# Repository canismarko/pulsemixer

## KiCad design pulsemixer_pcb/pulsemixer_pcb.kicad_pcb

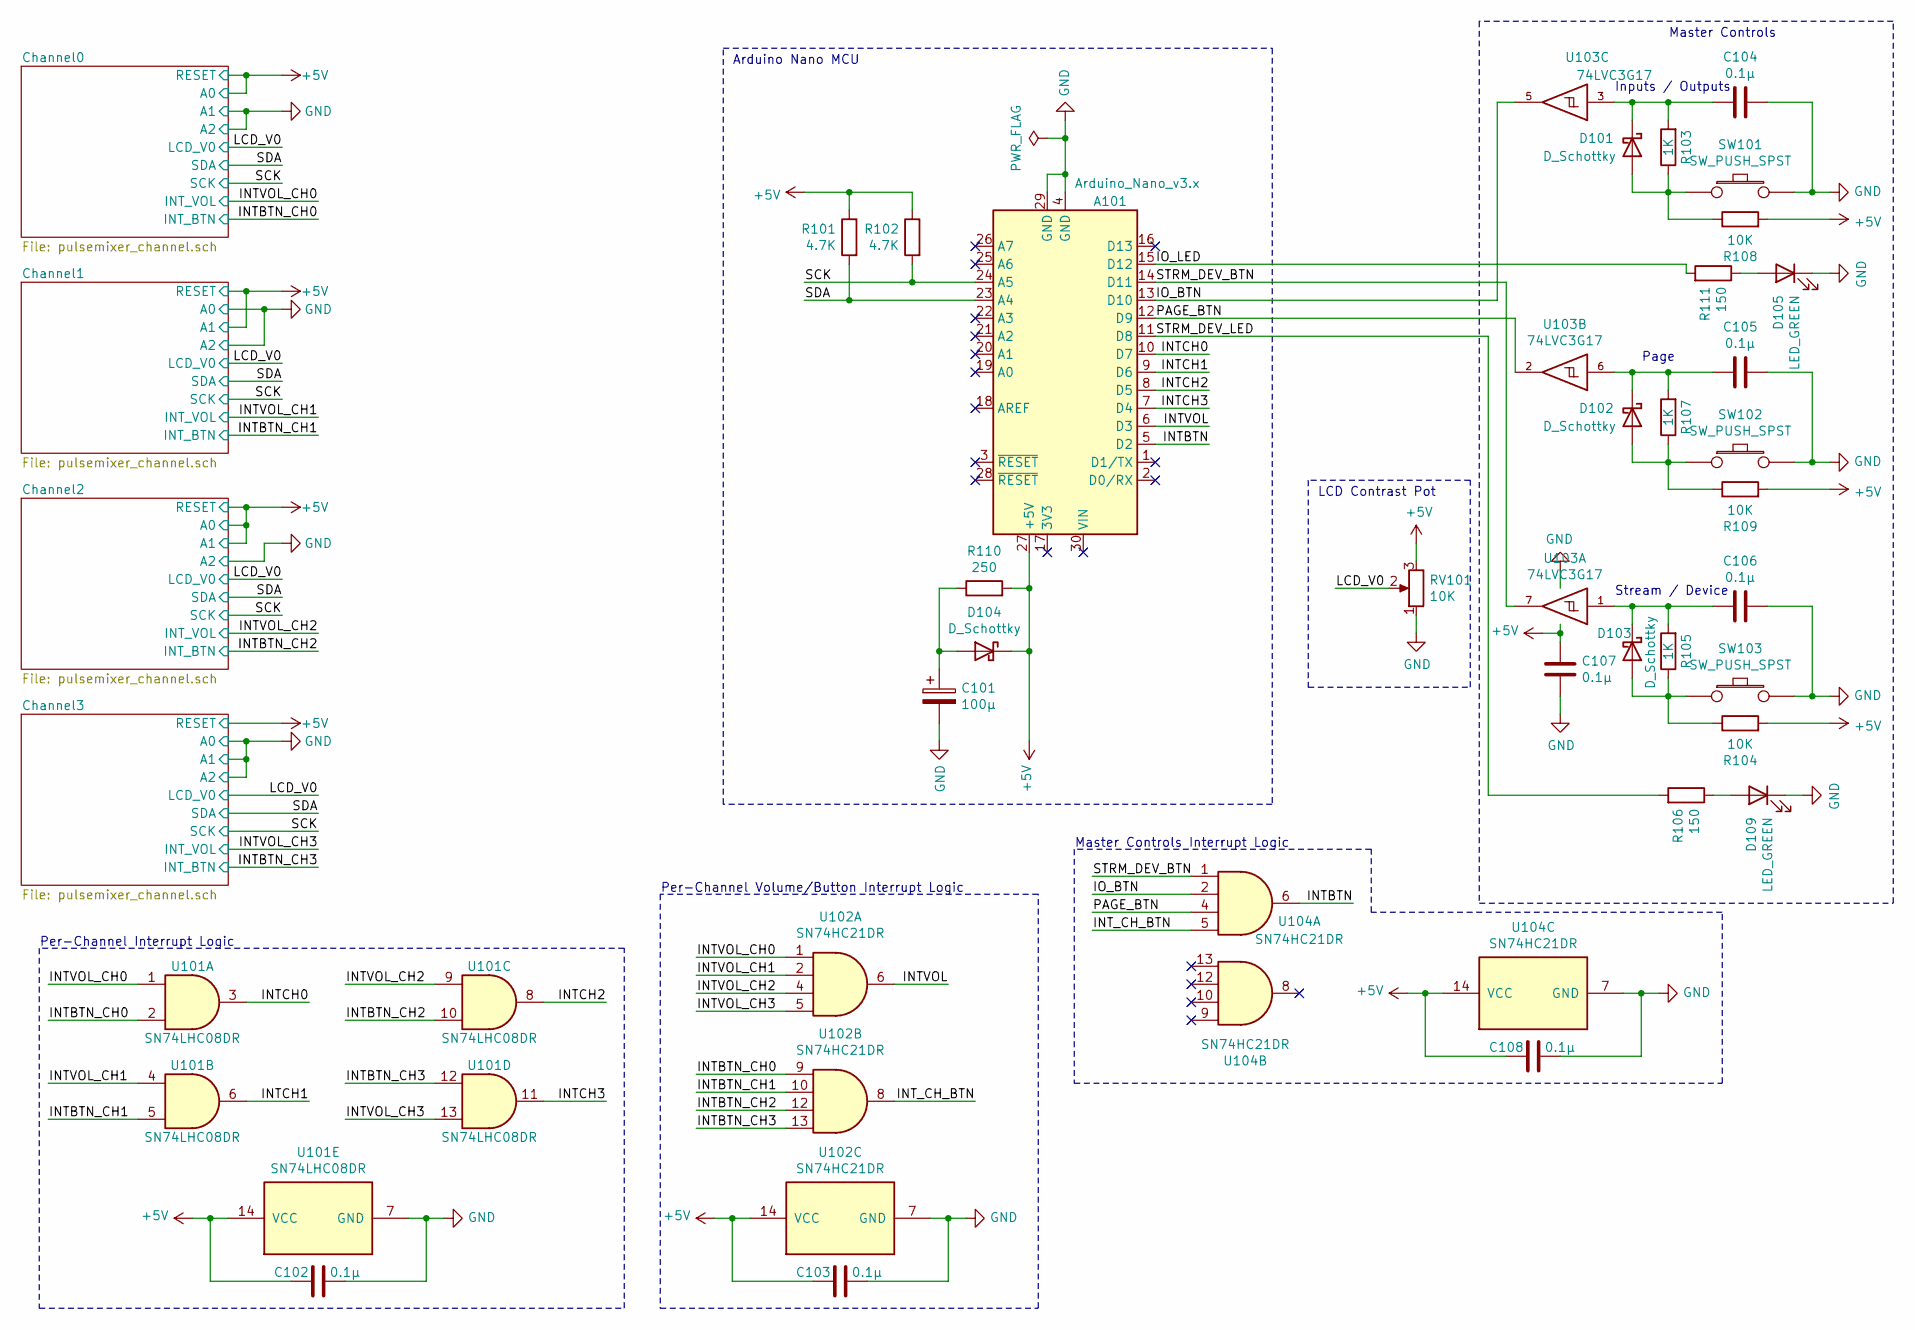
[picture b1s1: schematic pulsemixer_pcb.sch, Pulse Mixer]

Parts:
A101: Arduino_Nano_v3.x; SHIELD_ARDUINO_NANO
C101: 100µ; CP_Radial_D8.0mm_P3.50mm
C102, C103, C104, C105, C106, C107, C108: 0.1µ; C_0805_HandSoldering
D101, D102, D103, D104: D_Schottky; D_1206
D105, D109: LED_GREEN; LED_1206_HandSoldering
R101, R102: 4.7K; R_1206
R103, R105, R107: 1K; R_1206
R104, R108, R109: 10K; R_1206
R106, R111: 150; R_1206
R110: 250; R_1206
RV101: 10K; TRIM_3352T-1-103LF
SW101, SW102, SW103: SW_PUSH_SPST; SW_PUSH_6mm
U101: SN74LHC08DR; SOIC-14_3.9x8.7mm_Pitch1.27mm
U102, U104: SN74HC21DR; SOIC-14_3.9x8.7mm_Pitch1.27mm
U103: 74LVC3G17; SSOP-8_2.95x2.8mm_Pitch0.65mm

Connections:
+5V: A101.27 (+5V), C102.1, C103.1, C107.2, C108.2, D104.1 (K), R101.1, R102.1, R104.2, R108.2, R109.2, R110.2, RV101.3, U101.14 (VCC), U102.14 (VCC), U103.8 (VCC), U104.14 (VCC); also elsewhere on the board
/INTBTN: A101.5 (D2), U104.6
/INTBTN_CH0: U101.2, U102.9; also elsewhere on the board
/INTBTN_CH1: U101.5, U102.10; also elsewhere on the board
/INTBTN_CH2: U101.10, U102.12; also elsewhere on the board
/INTBTN_CH3: U101.12, U102.13; also elsewhere on the board
/INTCH0: A101.10 (D7), U101.3
/INTCH1: A101.9 (D6), U101.6
/INTCH2: A101.8 (D5), U101.8
/INTCH3: A101.7 (D4), U101.11
/INTVOL: A101.6 (D3), U102.6
/INTVOL_CH0: U101.1, U102.1; also elsewhere on the board
/INTVOL_CH1: U101.4, U102.2; also elsewhere on the board
/INTVOL_CH2: U101.9, U102.4; also elsewhere on the board
/INTVOL_CH3: U101.13, U102.5; also elsewhere on the board
/INT_CH_BTN: U102.8, U104.5
/IO_BTN: A101.13 (D10), U103.5, U104.2
/IO_LED: A101.15 (D12), R111.2
/LCD_V0: RV101.2; also elsewhere on the board
/PAGE_BTN: A101.12 (D9), U103.2, U104.4
/SCK: A101.24 (A5), R102.2; also elsewhere on the board
/SDA: A101.23 (A4), R101.2; also elsewhere on the board
/STRM_DEV_BTN: A101.14 (D11), U103.7, U104.1
/STRM_DEV_LED: A101.11 (D8), R106.2
GND: A101.4 (GND), A101.29 (GND), C101.2, C102.2, C103.2, C104.2, C105.2, C106.2, C107.1, C108.1, D105.1 (K), D109.1 (K), RV101.1, SW101.2, SW102.2, SW103.2, U101.7 (GND), U102.7 (GND), U103.4 (GND), U104.7 (GND); also elsewhere on the board
unnamed: C101.1, D104.2 (A), R110.1
unnamed: C104.1, D101.1 (K), R103.2, U103.3
unnamed: C105.1, D102.1 (K), R107.2, U103.6
unnamed: C106.1, D103.1 (K), R105.2, U103.1
unnamed: D101.2 (A), R103.1, R108.1, SW101.1
unnamed: D102.2 (A), R107.1, R109.1, SW102.1
unnamed: D103.2 (A), R104.1, R105.1, SW103.1
unnamed: D105.2 (A), R111.1
unnamed: D109.2 (A), R106.1

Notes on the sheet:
LCD Contrast Pot
Arduino Nano MCU
Per-Channel Interrupt Logic
Per-Channel Volume/Button Interrupt Logic
Master Controls
Stream / Device
Page
Inputs / Outputs
Master Controls Interrupt Logic

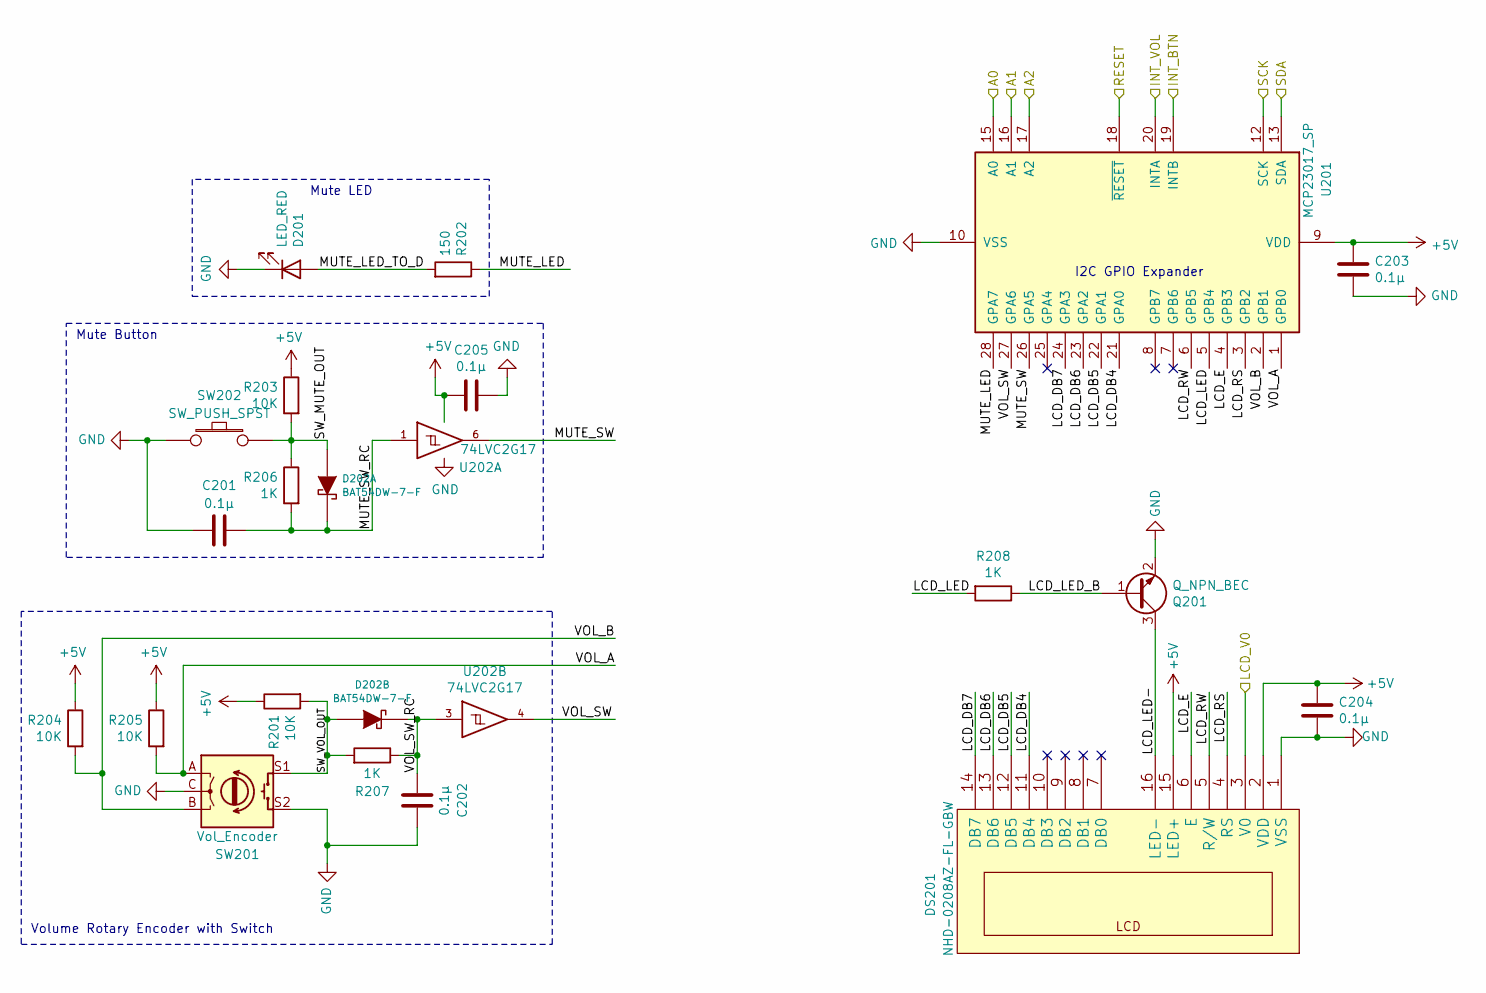
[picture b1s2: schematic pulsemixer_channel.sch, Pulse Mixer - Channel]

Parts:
C501, C502, C503, C504, C505: 0.1µ; C_0805_HandSoldering
D501: LED_RED; LED_1206_HandSoldering
D502: BAT54DW-7-F; Diode_Dual_SOT-23-6
DS501: NHD-0208AZ-FL-GBW
Q201: Q_NPN_BEC; SOT-23
R501, R503, R504, R505: 10K; R_1206
R502: 150; R_1206
R506, R507, R508: 1K; R_1206
SW501: Vol_Encoder; EN12-HS22AF18
SW502: SW_PUSH_SPST; SW_PUSH_6mm
U501: MCP23017_SP; DIP-28_W7.62mm
U502: 74LVC2G17; SOT-23-6

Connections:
+5V: C503.1, C504.1, C505.2, DS501.2 (VDD), DS501.15 (LED+), R501.1, R503.1, R504.1, R505.1, U501.9 (VDD), U501.15 (A0), U501.16 (A1), U501.18 (~RESET~), U502.5 (VCC); also elsewhere on the board
/Channel3/LCD_DB4: DS501.11 (DB4), U501.21 (GPA0)
/Channel3/LCD_DB5: DS501.12 (DB5), U501.22 (GPA1)
/Channel3/LCD_DB6: DS501.13 (DB6), U501.23 (GPA2)
/Channel3/LCD_DB7: DS501.14 (DB7), U501.24 (GPA3)
/Channel3/LCD_E: DS501.6 (E), U501.4 (GPB3)
/Channel3/LCD_LED: R508.2, U501.5 (GPB4)
/Channel3/LCD_RS: DS501.4 (RS), U501.3 (GPB2)
/Channel3/LCD_RW: DS501.5 (R/W), U501.6 (GPB5)
/Channel3/MUTE_LED: R502.1, U501.28 (GPA7)
/Channel3/MUTE_LED_TO_D: D501.2 (A), R502.2
/Channel3/MUTE_SW: U501.26 (GPA5), U502.6
/Channel3/MUTE_SW_RC: C501.2, D502.6 (C1), R506.2, U502.1
/Channel3/SW_MUTE_OUT: D502.1 (A1), R503.2, R506.1, SW502.1
/Channel3/SW_VOL_OUT: D502.4 (A2), R501.2, R507.2, SW501.S1
/Channel3/VOL_A: R505.2, SW501.A, U501.1 (GPB0)
/Channel3/VOL_B: R504.2, SW501.B, U501.2 (GPB1)
/Channel3/VOL_SW: U501.27 (GPA6), U502.4
/Channel3/VOL_SW_RC: C502.2, D502.3 (C2), R507.1, U502.3
/INTBTN_CH3: U501.19 (INTB); also elsewhere on the board
/INTVOL_CH3: U501.20 (INTA); also elsewhere on the board
/LCD_V0: DS501.3 (V0); also elsewhere on the board
/SCK: U501.12 (SCK); also elsewhere on the board
/SDA: U501.13 (SDA); also elsewhere on the board
GND: C501.1, C502.1, C503.2, C504.2, C505.1, D501.1 (K), DS501.1 (VSS), Q201.2 (E), SW501.C, SW501.S2, SW502.2, U501.10 (VSS), U501.17 (A2), U502.2 (GND); also elsewhere on the board

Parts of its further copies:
C201, C202, C203, C204, C205, C301, C302, C303, C304, C305, C401, C402, C403, C404, C405: 0.1µ; C_0805_HandSoldering
D201, D301, D401: LED_RED; LED_1206_HandSoldering
D202, D302, D402: BAT54DW-7-F; Diode_Dual_SOT-23-6
DS201, DS301, DS401: NHD-0208AZ-FL-GBW
Q301, Q401, Q501: Q_NPN_BEC; SOT-23
R201, R203, R204, R205, R301, R303, R304, R305, R401, R403, R404, R405: 10K; R_1206
R202, R302, R402: 150; R_1206
R206, R207, R208, R306, R307, R308, R406, R407, R408: 1K; R_1206
SW201, SW301, SW401: Vol_Encoder; EN12-HS22AF18
SW202, SW302, SW402: SW_PUSH_SPST; SW_PUSH_6mm
U201, U301, U401: MCP23017_SP; DIP-28_W7.62mm
U202, U302, U402: 74LVC2G17; SOT-23-6

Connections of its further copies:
+5V: C203.1, C204.1, C205.2, C303.1, C304.1, C305.2, C403.1, C404.1, C405.2, DS201.2 (VDD), DS201.15 (LED+), DS301.2 (VDD), DS301.15 (LED+), DS401.2 (VDD), DS401.15 (LED+), R201.1, R203.1, R204.1, R205.1, R301.1, R303.1, R304.1, R305.1, R401.1, R403.1, R404.1, R405.1, U201.9 (VDD), U201.18 (~RESET~), U202.5 (VCC), U301.9 (VDD), U301.15 (A0), U301.18 (~RESET~), U302.5 (VCC), U401.9 (VDD), U401.16 (A1), U401.18 (~RESET~), U402.5 (VCC); also elsewhere on the board
/Channel0/LCD_DB4: DS201.11 (DB4), U201.21 (GPA0)
/Channel0/LCD_DB5: DS201.12 (DB5), U201.22 (GPA1)
/Channel0/LCD_DB6: DS201.13 (DB6), U201.23 (GPA2)
/Channel0/LCD_DB7: DS201.14 (DB7), U201.24 (GPA3)
/Channel0/LCD_E: DS201.6 (E), U201.4 (GPB3)
/Channel0/LCD_LED: R208.2, U201.5 (GPB4)
/Channel0/LCD_RS: DS201.4 (RS), U201.3 (GPB2)
/Channel0/LCD_RW: DS201.5 (R/W), U201.6 (GPB5)
/Channel0/MUTE_LED: R202.1, U201.28 (GPA7)
/Channel0/MUTE_LED_TO_D: D201.2 (A), R202.2
/Channel0/MUTE_SW: U201.26 (GPA5), U202.6
/Channel0/MUTE_SW_RC: C201.2, D202.6 (C1), R206.2, U202.1
/Channel0/SW_MUTE_OUT: D202.1 (A1), R203.2, R206.1, SW202.1
/Channel0/SW_VOL_OUT: D202.4 (A2), R201.2, R207.2, SW201.S1
/Channel0/VOL_A: R205.2, SW201.A, U201.1 (GPB0)
/Channel0/VOL_B: R204.2, SW201.B, U201.2 (GPB1)
/Channel0/VOL_SW: U201.27 (GPA6), U202.4
/Channel0/VOL_SW_RC: C202.2, D202.3 (C2), R207.1, U202.3
/Channel1/LCD_DB4: DS301.11 (DB4), U301.21 (GPA0)
/Channel1/LCD_DB5: DS301.12 (DB5), U301.22 (GPA1)
/Channel1/LCD_DB6: DS301.13 (DB6), U301.23 (GPA2)
/Channel1/LCD_DB7: DS301.14 (DB7), U301.24 (GPA3)
/Channel1/LCD_E: DS301.6 (E), U301.4 (GPB3)
/Channel1/LCD_LED: R308.2, U301.5 (GPB4)
/Channel1/LCD_LED-: DS301.16 (LED-), Q301.3 (C)
/Channel1/LCD_LED_B: Q301.1 (B), R308.1
/Channel1/LCD_RS: DS301.4 (RS), U301.3 (GPB2)
/Channel1/LCD_RW: DS301.5 (R/W), U301.6 (GPB5)
/Channel1/MUTE_LED: R302.1, U301.28 (GPA7)
/Channel1/MUTE_LED_TO_D: D301.2 (A), R302.2
/Channel1/MUTE_SW: U301.26 (GPA5), U302.6
/Channel1/MUTE_SW_RC: C301.2, D302.6 (C1), R306.2, U302.1
/Channel1/SW_MUTE_OUT: D302.1 (A1), R303.2, R306.1, SW302.1
/Channel1/SW_VOL_OUT: D302.4 (A2), R301.2, R307.2, SW301.S1
/Channel1/VOL_A: R305.2, SW301.A, U301.1 (GPB0)
/Channel1/VOL_B: R304.2, SW301.B, U301.2 (GPB1)
/Channel1/VOL_SW: U301.27 (GPA6), U302.4
/Channel1/VOL_SW_RC: C302.2, D302.3 (C2), R307.1, U302.3
/Channel2/LCD_DB4: DS401.11 (DB4), U401.21 (GPA0)
/Channel2/LCD_DB5: DS401.12 (DB5), U401.22 (GPA1)
/Channel2/LCD_DB6: DS401.13 (DB6), U401.23 (GPA2)
/Channel2/LCD_DB7: DS401.14 (DB7), U401.24 (GPA3)
/Channel2/LCD_E: DS401.6 (E), U401.4 (GPB3)
/Channel2/LCD_LED: R408.2, U401.5 (GPB4)
/Channel2/LCD_LED-: DS401.16 (LED-), Q401.3 (C)
/Channel2/LCD_LED_B: Q401.1 (B), R408.1
/Channel2/LCD_RS: DS401.4 (RS), U401.3 (GPB2)
/Channel2/LCD_RW: DS401.5 (R/W), U401.6 (GPB5)
/Channel2/MUTE_LED: R402.1, U401.28 (GPA7)
/Channel2/MUTE_LED_TO_D: D401.2 (A), R402.2
/Channel2/MUTE_SW: U401.26 (GPA5), U402.6
/Channel2/MUTE_SW_RC: C401.2, D402.6 (C1), R406.2, U402.1
/Channel2/SW_MUTE_OUT: D402.1 (A1), R403.2, R406.1, SW402.1
/Channel2/SW_VOL_OUT: D402.4 (A2), R401.2, R407.2, SW401.S1
/Channel2/VOL_A: R405.2, SW401.A, U401.1 (GPB0)
/Channel2/VOL_B: R404.2, SW401.B, U401.2 (GPB1)
/Channel2/VOL_SW: U401.27 (GPA6), U402.4
/Channel2/VOL_SW_RC: C402.2, D402.3 (C2), R407.1, U402.3
/INTBTN_CH0: U201.19 (INTB); also elsewhere on the board
/INTBTN_CH1: U301.19 (INTB); also elsewhere on the board
/INTBTN_CH2: U401.19 (INTB); also elsewhere on the board
/INTVOL_CH0: U201.20 (INTA); also elsewhere on the board
/INTVOL_CH1: U301.20 (INTA); also elsewhere on the board
/INTVOL_CH2: U401.20 (INTA); also elsewhere on the board
/LCD_V0: DS201.3 (V0), DS301.3 (V0), DS401.3 (V0); also elsewhere on the board
/SCK: U201.12 (SCK), U301.12 (SCK), U401.12 (SCK); also elsewhere on the board
/SDA: U201.13 (SDA), U301.13 (SDA), U401.13 (SDA); also elsewhere on the board
GND: C201.1, C202.1, C203.2, C204.2, C205.1, C301.1, C302.1, C303.2, C304.2, C305.1, C401.1, C402.1, C403.2, C404.2, C405.1, D201.1 (K), D301.1 (K), D401.1 (K), DS201.1 (VSS), DS301.1 (VSS), DS401.1 (VSS), Q301.2 (E), Q401.2 (E), Q501.2 (E), SW201.C, SW201.S2, SW202.2, SW301.C, SW301.S2, SW302.2, SW401.C, SW401.S2, SW402.2, U201.10 (VSS), U201.15 (A0), U201.16 (A1), U201.17 (A2), U202.2 (GND), U301.10 (VSS), U301.16 (A1), U301.17 (A2), U302.2 (GND), U401.10 (VSS), U401.15 (A0), U401.17 (A2), U402.2 (GND); also elsewhere on the board

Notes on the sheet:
Volume Rotary Encoder with Switch
Mute Button
Mute LED
I2C GPIO Expander

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
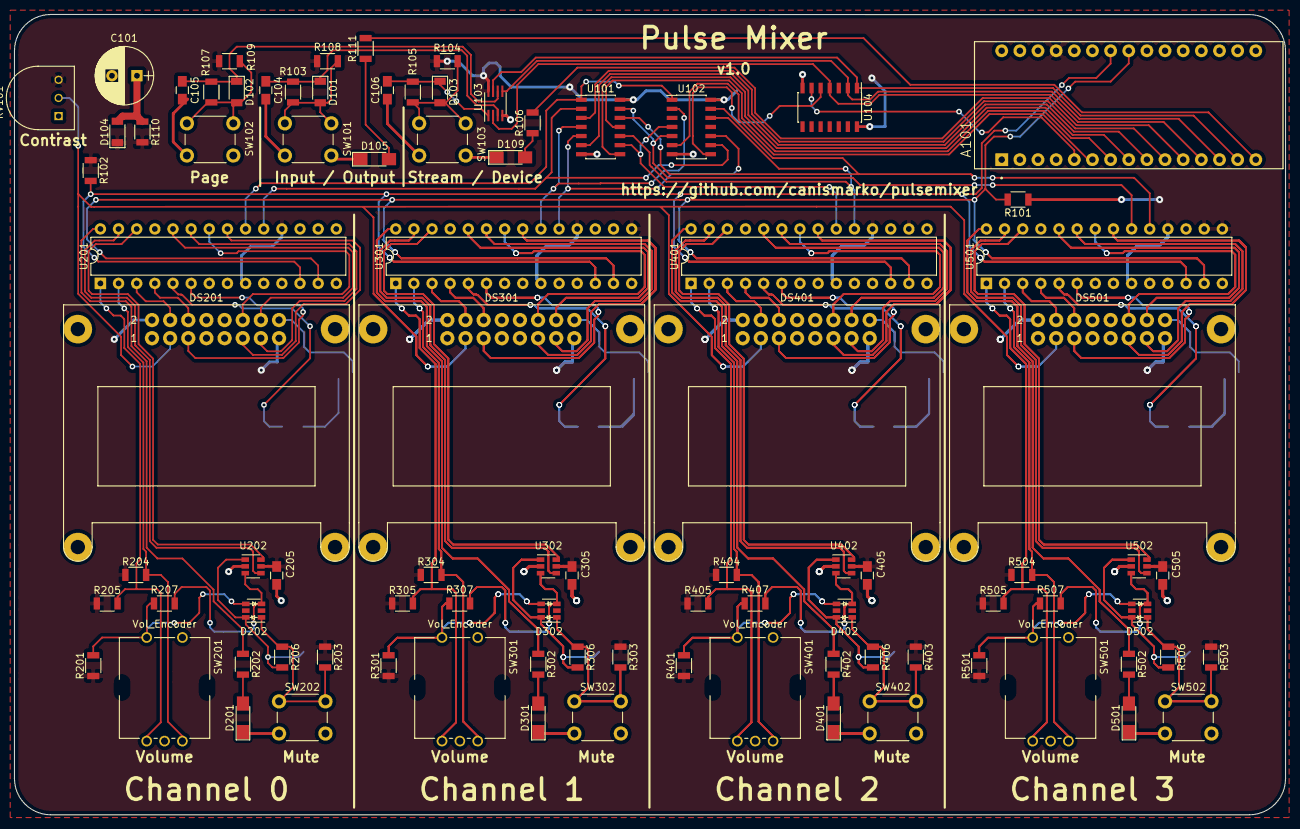
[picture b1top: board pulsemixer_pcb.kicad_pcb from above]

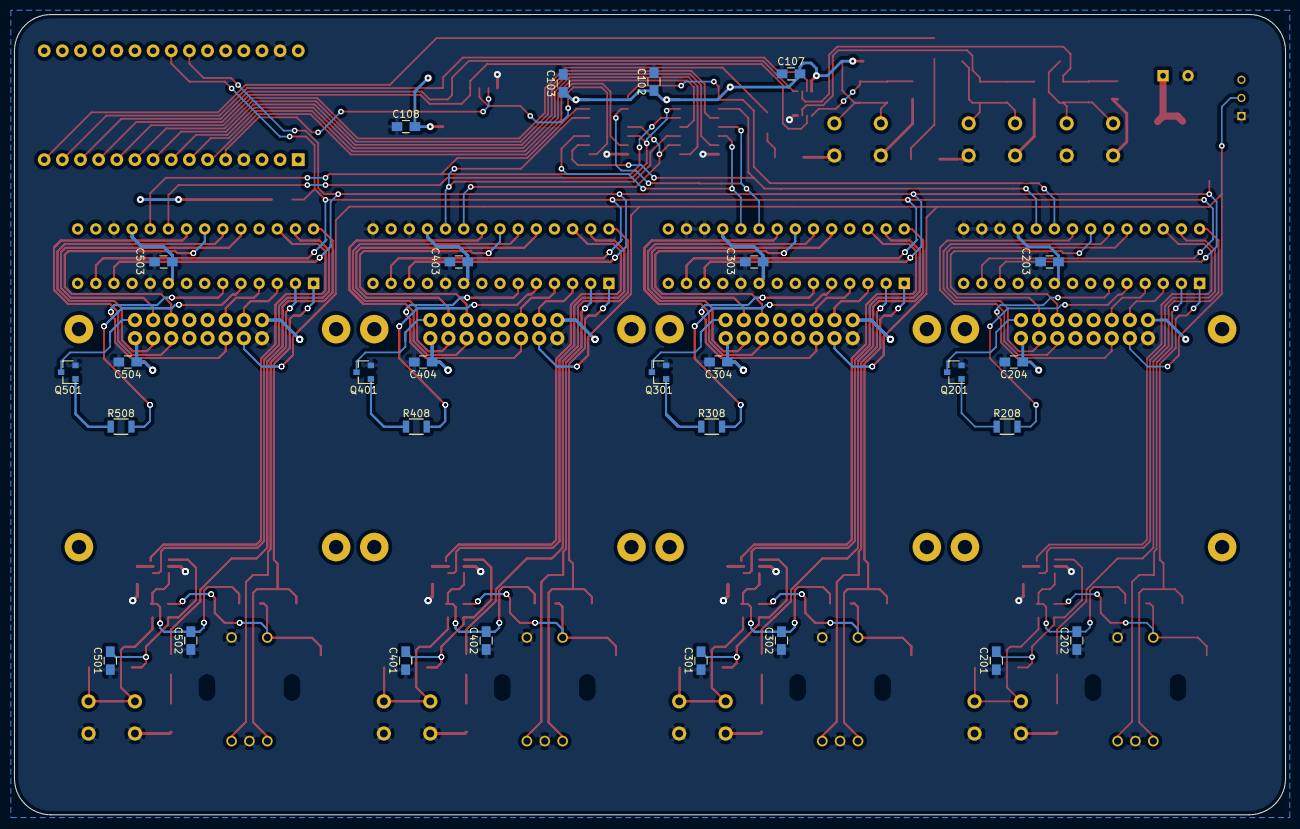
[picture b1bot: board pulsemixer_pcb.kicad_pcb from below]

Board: 2 copper layers, 177.9 x 112.0 mm, 118 parts (28 on the bottom side), 114 nets.

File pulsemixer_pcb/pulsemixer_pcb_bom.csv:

Id,Digi-Key Ln,Designator,Package,Quantity,Designation,Supplier and ref,
1,7,"DS201,DS401,DS501,DS301",NHD-0208AZ-FL-GBW,4,NHD-0208AZ-FL-GBW,‎NHD-0208AZ-FL-GBW,
2,3,"SW201,SW301,SW401,SW501",EN12-HS22AF18,4,Vol_Encoder,‎EN12-HS22AF18,
3,10,"C201,C202,C204,C203,C505,C405,C305,C205,C103,C102,C401,C402,C403,C404,C501,C502,C503,C504,C301,C302,C303,C304,C104,C105,C106,C107",C_0805_HandSoldering,27,0.1µ,‎C0805C104Z3VACTU,50 for price break
4,2,"U201,U401,U501,U301",DIP-28_W7.62mm,4,MCP23017_SP,‎MCP23017-E/SP,
5,20,"D201,D401,D501,D301",LED_1206_HandSoldering,4,LED_RED,CMD15-21VRD/TR8 ,Vf=2.1V @ 20mA
6,11,"SW202,SW103,SW402,SW502,SW302,SW101,SW102",SW_PUSH_6mm,7,SW_PUSH_SPST,PTS645SH43-2 LFS,
7,12,"U102, U104",SOIC-14_3.9x8.7mm_Pitch1.27mm,2,SN74HC21DR,SN74HC21DR,
8,4,U101,SOIC-14_3.9x8.7mm_Pitch1.27mm,1,SN74LHC08DR,SN74HC08DR,
9,22,A101,SHIELD_ARDUINO_NANO,1,Arduino_Nano_v3.x,‎A000005‎,Not ordered since I already have one
10,21,"D109,D105",LED_1206_HandSoldering,2,LED_GREEN,CMD15-21VGD/TR8,Vf=2.1V @ 20mA
11,6,RV101,TRIM_3352T-1-103LF,1,10K,‎3352T-1-103LF‎,
12,13,"D101,D102,D103,D104",D_1206,4,D_Schottky,SD1206S040S0R5 ,
13,8,U103,SSOP-8_2.95x2.8mm_Pitch0.65mm,1,74LVC3G17,‎SN74LVC3G17DCTR,
14,5,"D202,D302,D402,D502",Diode_Dual_SOT-23-6,4,BAT54DW-7-F,BAT54DW-7-F,
15,14,"Q201,Q301,Q401,Q501",SOT-23,4,Q_NPN_BEC,MMBT3904-7-F,
16,9,"U202,U302,U402,U502",SOT-23-6,4,74LVC2G17,‎SN74LVC2G17DBVR,
17,1,C101,CP_Radial_D8.0mm_P3.50mm,1,100µ,‎UMV1E100MFD1TP,
18,15,"R101,R102",R_1206,2,4.7K,RC1206FR-074K7L,
19,16,"R103,R105,R107,R206,R207,R208,R306,R307,R308,R406,R407,R408,R506,R507,R508",R_1206,15,1K,RNCP1206FTD1K00,
20,17,"R104,R108,R109,R201,R203,R204,R205,R301,R303,R304,R305,R401,R403,R404,R405,R501,R503,R504,R505",R_1206,19,10K,RC1206FR-0710KL,
21,18,"R106,R202,R302,R402,R502,R111",R_1206,6,150,311-150FRCT-ND ,
22,19,R110,R_1206,1,250,RMCF1206FT270R ,
23,,,6mm diameter with 4.5mm flat,4,Knob,1722-1238-ND ,

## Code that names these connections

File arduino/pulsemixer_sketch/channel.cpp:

#include "Arduino.h"
#include "channel.h"
#include "GPIO.h"

// #define DEBUG

#define MUTE_LED 0x8000 // B10000000 00000000
#define VOL_SW   0x4000 // B01000000 00000000
#define MUTE_SW  0x2000 // B00100000 00000000
#define VOL_A    0x0001 // B00000000 00000001
#define VOL_B    0x0002 // B00000000 00000010
#define VOLS     (VOL_A | VOL_B)

#define MIN_VOL 0
#define MAX_VOL 100

volatile boolean isr_is_running = false;


const byte RotaryDecodeTable[4][4] = {  // Declare array RotaryDecodeTable
{B00, B10, B01, B11},
{B01, B00, B11, B10},
{B10, B11, B00, B01},
{B11, B01, B10, B00}
};


gpio_bank Channel::getAddr() {
  return _addr;
}


void Channel::setupI2C(gpio_bank new_addr) {
  // Save the I2C address for later operations
  _addr = new_addr;
  _gpio.setupI2C(_addr);
  // _short_name = "Addr: " + String(_addr, HEX);
  // Set pins to read/write
  // Input pins
  gpio_full iodir = 0x0000;
  gpio_full io_mask = MUTE_LED | VOL_SW | MUTE_SW | VOL_A | VOL_B;
  iodir = iodir | MUTE_SW;
  iodir = iodir | VOL_SW;
  iodir = iodir | VOL_A;
  iodir = iodir | VOL_B;
  // Output pins
  iodir = iodir & ~MUTE_LED;
  _gpio.setRegister(IODIRA, iodir, io_mask);

  // Set up hardware interrupts
  // writeMCP(_addr, GPINTENA, (gpio_bank) B00000000);
  // writeMCP(_addr, GPINTENB, (gpio_bank) B00000000);
  // writeMCP(_addr, INTCONA, (gpio_bank) 0x00);
  // writeMCP(_addr, INTCONB, (gpio_bank) B00000000);
  _gpio.enableInterrupts(VOL_A | VOL_B);
  _gpio.enableInterrupts(VOL_SW | MUTE_SW);

  // Make buttons report 1 when pressed
  // writeMCP(_addr, IPOLB, (gpio_bank) B00000011);

  // Prepare the LCD to display channel name, etc.
  _lcd.setupI2C(_addr);
  showChannelName();

}

void Channel::showChannelName() {
  _lcd.setLineOne(_short_name);
}
  

void Channel::writeGPIO(gpio_full data) {
  _gpio.writeMCP(_addr, GPIOA, data);
}


void Channel::setInterruptFlag() {
  // Checker to see if we're already in an ISR
  if(isr_is_running || _gpio.is_busy()) return; //we have been interrupted while already processing an interrupt - ignore this ocurrence
  _interrupt_flag = true;
  isr_is_running = true;
  interrupts(); //re-enable interrupts so that interrupt-based functions can be used inside this function
  // Check if this is a volume knob event
  gpio_full int_state = readInterruptState();
  // Determine which inputs triggered the interrupt
  // gpio_full int_triggered = readInterruptFlags();
  // Disable interrupts so we can keep running this function
  
  isr_is_running = false;
  // Extract the volume rotary encoder A/B bits
  byte new_vols = (int_state & VOLS);
  byte vol_move = RotaryDecodeTable[_vol_old_pins][new_vols]; // used RotaryDecodeTable to decide movement, if any
  _vol_old_pins = new_vols;
  // Set the pending volume to the current volume if it's not dirty
  if (!_volume_dirty)
    pending_volume = _volume;
  if (vol_move == B10){ // if result was move right (CW), increment counter
    pending_volume += 3;
    _volume_dirty = true;
  }
  if (vol_move == B01){ // if result was move left (anti-CW), decrement counter
    pending_volume -= 3;
    _volume_dirty = true;
  }
  noInterrupts(); //turn off interrupts so we can't be interrupted while resetting our special variable
  
}


void Channel::setVolume(int new_volume) {
  unsigned long current_time = micros();
  if (current_time - _last_volume_change > 10000) {
    if (new_volume < MIN_VOL) {
      new_volume = MIN_VOL;
    } else if (new_volume > MAX_VOL) {
      new_volume = MAX_VOL;
    }
    #ifdef DEBUG
    Serial.print("Setting new volume ");
    Serial.print(_id);
    Serial.print(": ");
    Serial.println(new_volume);
    #endif
    _volume = new_volume;
    pending_volume = _volume;
    // Update the LCD
    _lcd.showVolume(_volume);
    _lcd.turnOnLED();
    // Send new volume to the host
    Serial.print("!set volume ");
    Serial.print(_id);
    Serial.print(" ");
    Serial.println(_volume);
  }
  _last_volume_change = current_time;
}


void Channel::bumpVolume(int vol_change) {
  setVolume(_volume + vol_change);
}


void Channel::updateOutputs() {
  _lcd.updateDisplay();
}


bool Channel::processInterrupts() {
  if (_volume_dirty) {
    _volume_dirty = false;
    #ifdef DEBUG
    Serial.print("Volume changed: ");
    Serial.println(pending_volume);
    #endif
    // _volume = bumpVolume(pending_volume);
    Channel::setVolume(pending_volume);
  }
  // Returns true if the volume encoder was moved
  if (_interrupt_flag) {
    _interrupt_flag = false;
    gpio_full int_state = readInterruptState();
    // Determine which inputs triggered the interrupt
    gpio_full int_triggered = readInterruptFlags();
    // Extract the volume rotary encoder A/B bits
//    byte new_vols = (int_state & VOLS);
//    if (new_vols != _vol_old_pins)
//      _last_volume_touched = micros();
//    byte vol_move = RotaryDecodeTable[_vol_old_pins][new_vols]; // used RotaryDecodeTable to decide movement, if any
//    _vol_old_pins = new_vols;
//    if (vol_move == B10){ // if result was move right (CW), increment counter
//      bumpVolume(1);
//    }
//    if (vol_move == B01){ // if result was move left (anti-CW), decrement counter
//      bumpVolume(-1);
//    }
  
    if (~int_state & MUTE_SW) {
      // Serial.println("Mute switch pressed");
      toggleMute();
    }
    if (~int_state & VOL_SW) {
      // Serial.println("Volume switch pressed");
      _lcd.turnOnLED();
    }
  }
  return (micros() - _last_volume_touched < 20000);
}


gpio_full Channel::readInterruptState() {
  // Read the state of all the GPIO expander pins when the last
  // interrupt was triggered. This also clears the
  // interrupt pin.
  gpio_full int_state = _gpio.readFullRegister(INTCAPA);
  return int_state;
}

gpio_full Channel::readInterruptFlags() {
  // Read the interrupt flags showing which pins in the GPIO expander 
  // triggered the last interrupt. This does not clear the
  // interrupt pin.
  gpio_full int_state = _gpio.readFullRegister(INTFA);
  return int_state;
}



void Channel::setMute(bool new_mute_state) {
  _isMuted = new_mute_state;
  if (_isMuted) {
    _gpio.setPins(GPIOA, 0xFFFF, MUTE_LED);
    _lcd.setLineTwo("Muted   ");
  } else {
    _gpio.setPins(GPIOA, 0x0000, MUTE_LED);
    _lcd.setLineTwo("Unmuted ");
  }
  _lcd.writeLines();
  _lcd.turnOnLED();
}


void Channel::toggleMute() {
  bool new_mute_state = !_isMuted;
  setMute(new_mute_state);
  // Notify the host
  Serial.print("!mute ");
  Serial.print(_id);
  Serial.print(" ");
  Serial.println(_isMuted);
}


void Channel::setShortName(String new_name) {
  _short_name = new_name;
  showChannelName();
}

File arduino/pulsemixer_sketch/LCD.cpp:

#include "LCD.h"
#include "GPIO.h"

#define LCD_DB      0x0FF0 // B00001111 11110000 // 8-bit mode
#define LCD_DB_4BIT 0x0F00 // B00001111 00000000 // 4-bit mode
#define LCD_ENABLE  0x0008 // B00000000 00001000
#define LCD_RS      0x0004 // B00000000 00000100
#define LCD_RW      0x0020 // B00000000 00100000
#define LCD_LED     0x0010 // B00000000 00010000
#define LCD_DATA LCD_DB_4BIT | LCD_ENABLE | LCD_RS | LCD_RW
#define LCD_ALL LCD_DATA | LCD_LED

#define LED_TIMEOUT 5000 // In milliseconds
#define LCD_WIDTH 8

// #define DEBUG


void LCD::setupI2C(gpio_bank addr)
{
  _addr = addr;
  _gpio.setupI2C(addr);
  // Set GPIO I/O settings
  gpio_full iodir = 0x0000;
  iodir = iodir & ~LCD_DB_4BIT;
  iodir = iodir & ~LCD_ENABLE;
  iodir = iodir & ~LCD_LED;
  iodir = iodir & ~LCD_RW;
  gpio_full iodir_mask = LCD_ALL;
  _gpio.setRegister(IODIRA, iodir, iodir_mask);
  // Initalize the LCD display
  this -> _init();
  // Start with the LEDs off
  this -> turnOffLED();
}


void LCD::setLineOne(String new_text)
{
  // Add extra spaces as necessary
  while(new_text.length() < LCD_WIDTH) {
    new_text += ' ';
  }
  #ifdef DEBUG
  Serial.print("Setting line two to: ");
  Serial.println(new_text);
  #endif
  _line_one_text = new_text;
}


void LCD::setLineTwo(String new_text)
{
  // Add extra spaces as necessary
  while(new_text.length() < LCD_WIDTH) {
    new_text += ' ';
  }
  #ifdef DEBUG
  Serial.print("Setting line two to: ");
  Serial.println(new_text);
  #endif
  _line_two_text = new_text;
}


void LCD::showVolume(int new_vol)
{
  unsigned char line_length;
  String message = String(new_vol) + "%    ";
  // Pad the message with leading spaces
  for (int i=0; i<9-message.length(); i++) {
    message = " " + message;
  }
  setLineTwo(message);
  this->writeLines();
}


void LCD::updateDisplay()
// Check if the display has changed since it was last refreshed
// If nothing has changed, the display will not be written to.
{
  if (this->led_on) {
    // Check if the LED timer has expired
    unsigned long current_timer = millis() - led_on_time;
    if (current_timer > LED_TIMEOUT) {
      // Timeout has expired, so turn off the LED
      #ifdef DEBUG
      Serial.println("LED timer expired.");
      #endif
      setLineTwo("        ");
      this->writeLines();
      turnOffLED();
    }
  }
  this->writeLines();
}


void LCD::turnOnLED()
{
  
  this->led_on_time = millis();
  if (!this->led_on) {
    this->led_on = true;
    this->setLED(HIGH);
  }
  #ifdef DEBUG
  Serial.print("Turned on LED ");
  Serial.print(_addr, HEX);
  Serial.print(": ");
  Serial.println(this->led_on);
  #endif
  
}


void LCD::turnOffLED()
{
  this->led_on = false;
  this->setLED(LOW);
  #ifdef DEBUG
  Serial.print("Turned off LED ");
  Serial.print(this->_addr, HEX);
  Serial.print(": ");
  Serial.println(this->led_on);
  #endif
}


void LCD::setLED(bool setOn)
{
  gpio_full newState;
  if (setOn) {
    newState = 0xFFFF;
  }
  else {
    newState = 0x0000;
  }
  #ifdef DEBUG
  Serial.print("Sending LED command: ");
  Serial.println(newState, HEX);
  #endif
  this->_gpio.setPins(GPIOA, newState, LCD_LED);
  delay(500);
}


unsigned char LCD::_send_message(String message, String old_message, unsigned char cursor_offset)
{
  unsigned char line_length, cursor_pos=-1, characters_changed=0;
  line_length = min(message.length(), LCD_WIDTH);
  for (int i=0; i<line_length; i++) {
    // Check if the character needs to be updated
    if (message[i] != old_message[i]) {
      if ((i+cursor_offset) != cursor_pos) {
        // We've skipped some characters to update the cursor position
        cursor_pos = i+cursor_offset;
        _moveCursor(cursor_pos);
      }
      #ifdef DEBUG
      Serial.print("Printing char ");
      Serial.print(i);
      Serial.print(" (");
      Serial.print(cursor_pos);
      Serial.print(") to '");
      Serial.print(message[i]);
      Serial.println("'");
      #endif
      _send_data(message[i]);
      characters_changed += 1;
      cursor_pos++;
    }
  }
  return characters_changed;
}


void LCD::writeLines()
{
  
  if (_is_ready) {
    unsigned char blocks_changed=0;
    // Return home
    // _send_command(0x02); // B00000010
    _moveCursor(0);
    // Write line 1
    blocks_changed += _send_message(_line_one_text, _line_one_text_old, 0);
    // Write line 2
    blocks_changed += _send_message(_line_two_text, _line_two_text_old, 40);
    // Save the written text for next time
    _line_one_text_old = _line_one_text;
    _line_two_text_old = _line_two_text;
    // Light up the LED if anything changed
    if (blocks_changed > 0) {
      this->turnOnLED();
    }
  }
}


void LCD::_moveCursor(unsigned char pos)
{
  _send_command(128 + pos);
}


void LCD::_send_command(gpio_bank command, bool is4bit=true)
{
  gpio_full gpioPins = this->_gpio.readPins();
  // Put first (MSB) 4-bits of command on output port
  gpioPins = setBits(gpioPins, command << 4, LCD_DB_4BIT);
  // D/I=LOW : send instruction (D_I =0)
  gpioPins = setBits(gpioPins, 0x0000, LCD_RS);
  // R/W=LOW : Write (R_W =0)
  gpioPins = setBits(gpioPins, 0x0000, LCD_RW);
  // Clock enable: falling edge
  this->_gpio.setPins(GPIOA, gpioPins, LCD_ALL);
  _trigger();
  // Send the second (LSB) 4-bit chunk
  if (is4bit) {
    gpioPins = setBits(gpioPins, command << 8, LCD_DB_4BIT);
    this->_gpio.setPins(GPIOA, gpioPins, LCD_ALL);
    _trigger();
  }
}


void LCD::_send_data(gpio_bank data)
{
  gpio_full gpioPins = 0x0000;
  // Put first (MSB) 4-bits of data on output port
  gpioPins = setBits(gpioPins, data << 4, LCD_DB_4BIT);
  // D/I=HIGH : send data (D_I =1)
  gpioPins = setBits(gpioPins, 0xFFFF, LCD_RS);
  // R/W=LOW : Write (R_W =0)
  this -> _gpio.setPins(GPIOA, gpioPins, LCD_DATA);
  //Clock enable: falling edge
  _trigger();
  // Send the second (LSB) 4-bit chunk
  gpioPins = setBits(gpioPins, data << 8, LCD_DB_4BIT);
  this->_gpio.setPins(GPIOA, gpioPins, LCD_DATA);
  _trigger();
}


void LCD::_init()
{
  this -> _gpio.setPins(GPIOA, 0x0000, LCD_ENABLE);
  //Wait >40 msec after power is applied
  delay(100);
  // command 0x30 = Wake up
  _send_command(0x30, false); // B00110000
  // must wait 5ms, busy flag not available
  delay(30);
  // command 0x30 = Wake up #2
  _send_command(0x30, false); // B00110000
  // must wait 160us, busy flag not available
  delay(10);
  // command 0x30 = Wake up #3
  _send_command(0x30, false); // B00110000
  //must wait 160us, busy flag not available
  delay(10);
  // Function set: 4-bit
  _send_command(0x20, false); // B00100000
  // Function set: 4-bit/2-line
  _send_command(0x28); // B00101000
  // Set cursor
  _send_command(0x10); // B00010000
  // _send_command(B00011100); // B00011100
  #ifdef DEBUG
  // Display ON; Cursor ON; Blinking OFF
  _send_command(0x0E); // B00001110
  #else
  // Display ON; Cursor OFF; Blinking OFF
  _send_command(0x0C); // B00001100
  #endif
  // Entry mode set
  _send_command(0x06); // B00000110
  // Clear the display
  _send_command(0x01); // B00000001
  // Return home
  _send_command(0x02); // B00000010
  _is_ready = true;
}  


void LCD::_trigger()
{
  // Send the enable pulse to trigger the LCD
  this -> _gpio.setPins(GPIOA, 0xFFFF, LCD_ENABLE);
  delay(1);
  this -> _gpio.setPins(GPIOA, 0x0000, LCD_ENABLE);
}

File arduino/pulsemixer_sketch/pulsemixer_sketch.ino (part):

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#define PIN_INT_CH2 5
#define PIN_INT_CH3 4
int channel_pins[] = {PIN_INT_CH0, PIN_INT_CH1, PIN_INT_CH2, PIN_INT_CH3};
#define PIN_PAGE_BTN 9
#define PIN_IO_BTN 10
#define PIN_IO_LED 12
#define PIN_STREAM_DEV_BTN 11
#define PIN_STREAM_DEV_LED 8

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void isr_master_button_and_volume() {
  // Serial.println("Vol int called");
  // Master section buttons and volume rotary encoders got mixed together, so sort them out
  if (digitalRead(PIN_PAGE_BTN) == LOW) {
    page_button_pressed = true;
  } else if (digitalRead(PIN_IO_BTN) == LOW) {
    io_button_pressed = true;
  } else if (digitalRead(PIN_STREAM_DEV_BTN) == LOW) {
    stream_dev_button_pressed = true;
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

void updateMasterOutputs() {
  digitalWrite(PIN_IO_LED, io_flag);
  digitalWrite(PIN_STREAM_DEV_LED, stream_dev_flag);  
}

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  pinMode(PIN_INT_CH1, INPUT);
  pinMode(PIN_INT_CH2, INPUT);
  pinMode(PIN_INT_CH3, INPUT);
  pinMode(PIN_PAGE_BTN, INPUT);
  pinMode(PIN_IO_BTN, INPUT);
  pinMode(PIN_IO_LED, OUTPUT);
  pinMode(PIN_STREAM_DEV_BTN, INPUT);
  pinMode(PIN_STREAM_DEV_LED, OUTPUT);
  attachInterrupts();
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
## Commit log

2020-06-21 Initial basic design, firmware and software for breadboard mixer.
2020-06-29 Finished inital schematic, and a little bit of PCB layout.
2020-07-03 Revised schematic after testing rotary encoder.
2020-07-05 Simple reading of rotary encoder through the GPIO expander, with interrupts.
2020-07-12 Added object-oriented tools and added code for LCD.
2020-07-13 Rearranged LCD pins to allow for interrupts on both GPIO banks.
2020-07-13 Firmware code to turn LCD backlight on and off.
2020-07-25 Finished full PCB layout.
2020-07-27 Added another AND gate to include master section buttons in the buttn interrupt logic.
2020-08-07 Finalized changes to board and sent for fabrication.
2020-08-16 Wrote firmware skeleton for interacting with channel hardware.
2020-10-23 Initial firmware/controller that sends channel names and responds to mute requests.
2020-10-25 Host can now set intial volumes on the controller.
2020-10-26 Host can now send mute to the controller at startup.
